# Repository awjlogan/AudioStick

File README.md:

# AudioStick

Quality audio carrier board for the Raspberry Pi Zero. A self facilitating media node.

## Description and Getting Started

This board is designed to be used with a Raspberry Pi Zero (W) to turn it into small high quality streaming audio device. It incorporates a soft power switch, which makes it easier to use in normal settings (e.g., don't need to SSH in to shutdown) and prolong the life of the SD card. The AudioStick connects directly to the standard Raspberry Pi 40pin GPIO header.

All design files and source code are under the [_Don't Be A Dick_][dbad-github] license.

### Installation on the Raspberry Pi

From a clean installation of Raspbian, log in to your Raspberry Pi and run the following 3 lines:

```shell
> sudo apt install git
> git clone https://github.com/awjlogan/audiostick.git
> cd ./audiostick
> sudo ./audiostick_setup.sh
```

The `audiostick_setup.sh` script will:
 - Install the PCM5102's configuration in the boot configuration
 - Add the `asound.conf` configuration file
 - Add the power control service
 - Shutdown the Raspberry Pi

When it is complete, you will need to remove and reconnect the power before powering on again.

### Using the AudioStick

 - When the AudioStick is off, there is no power supplied to the Raspberry Pi, so power consumption is minimised.
 - Pressing the button will power on the Raspberry Pi. The power LED will flash until the Raspberry Pi has successfully booted, at which point it will stay on.
 - To turn the AudioStick OFF, press and hold the button for at least one second. The power LED will flash until the Raspberry Pi has safely shutdown. Once the LED returns to pulsing, the Raspberry Pi is completely off and it is safe to remove the power if you wish.

### Raspberry Pi Setup

The AudioStick is intended to be used with something like MPD to allow you to connect up to any speaker (with amplifier) and get access to your local music or streaming services controlled by your phone. There are a lot of good tutorials (REVISIT add some links) available, so I won't reiterate the points here, but here are a few additional things that might be useful:

 - Change the Raspberry Pi's hostname to a meaningful name, for example `livingroompi`. This will also allow you to have multiple AudioSticks on the same network.
 - Configure your NAS (or whatever storage) to mount at boot time in `/etc/fstab`. Be aware that the system might attempt to mount the device before the network is available.
 - Disable the swap file to increase the SD card's life (`sudo apt remove dphys-swapfile`)

## Hardware

### PCB

The PCB was designed using [EAGLE][eagle-web] v9. The *.brd* and *.sch* files are provided, along with a small library of parts (*AudioStick.lbr*). A full bill of materials is provided as an *.ods* file.

### Firmware and flashing the ATtiny13A

The source for the power control microcontroller is provided, and can be compiled with the supplied Makefile. You will need to alter `Makefile` with the programmer that you are using. To compile the firmware:

`> /firmware/make`

The header **J4** on the PCB is a standard Microchip \[Atmel\] 6 pin programming header. Using your compiled firmware (or the precompiled *.hex* file), you can flash the microcontroller with e.g. an Atmel ICE. To flash the microcontroller, run:

`> /firmware/make flash`

## Change Notes

### Version 2.2

 - [x] -ELEC- Change from pogo pads to pin header for AVR ISP.

### Version 2.1

 - [x] -MECH- Mirror RasPi so connectors face Audiostick board.
 - [x] -ELEC- Move LED to PWM output pin for more interesting effects (chicken transistor in case programmer can't drive pin with LED).
 - [x] -ELEC- Remove MOSFET power switch for RasPi. Use inrush inhibitor instead.
 - [x] -ELEC- Downsize RasPi power capacitor.

### Version 2.0

Finalised release PCB, firmware, and RasPi software.

## Datasheets and useful links

- [PCM5102 DAC][pcm5102-datasheet]
- [ATtiny13A][attiny13-datasheet]

[dbad-github]: https://github.com/philsturgeon/dbad
[eagle-web]: https://www.autodesk.com/products/eagle/overview
[pcm5102-datasheet]: http://www.ti.com/product/PCM5102
[attiny13-datasheet]: https://www.microchip.com/wwwproducts/en/ATTINY13A

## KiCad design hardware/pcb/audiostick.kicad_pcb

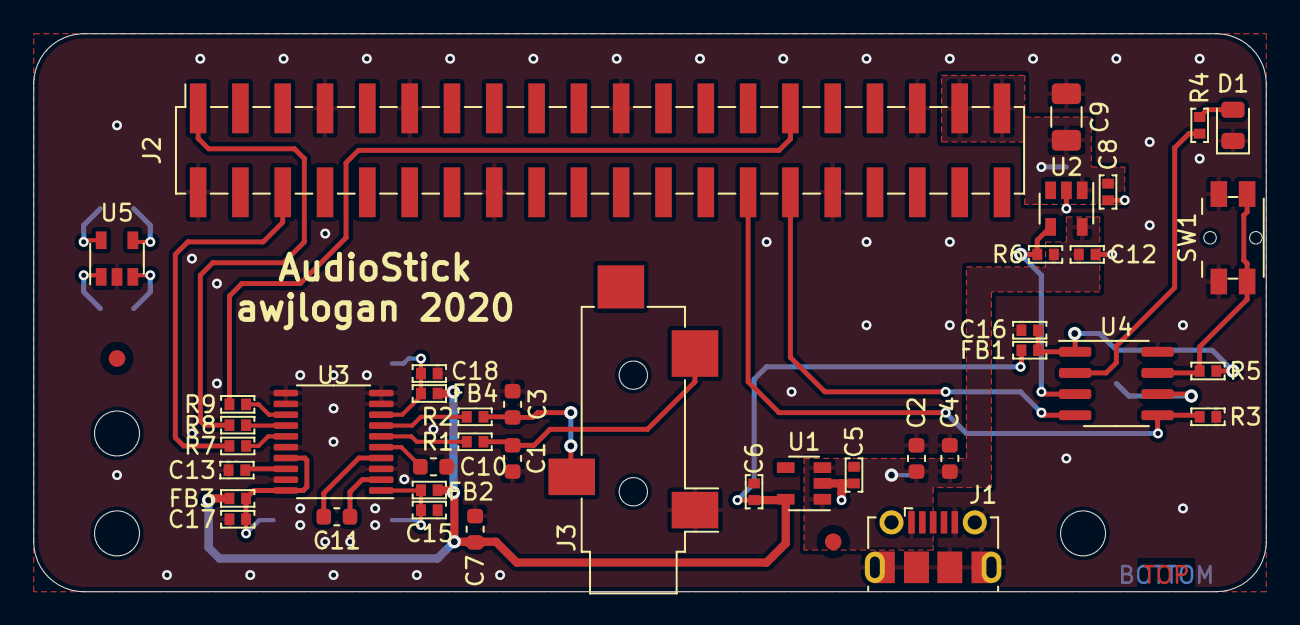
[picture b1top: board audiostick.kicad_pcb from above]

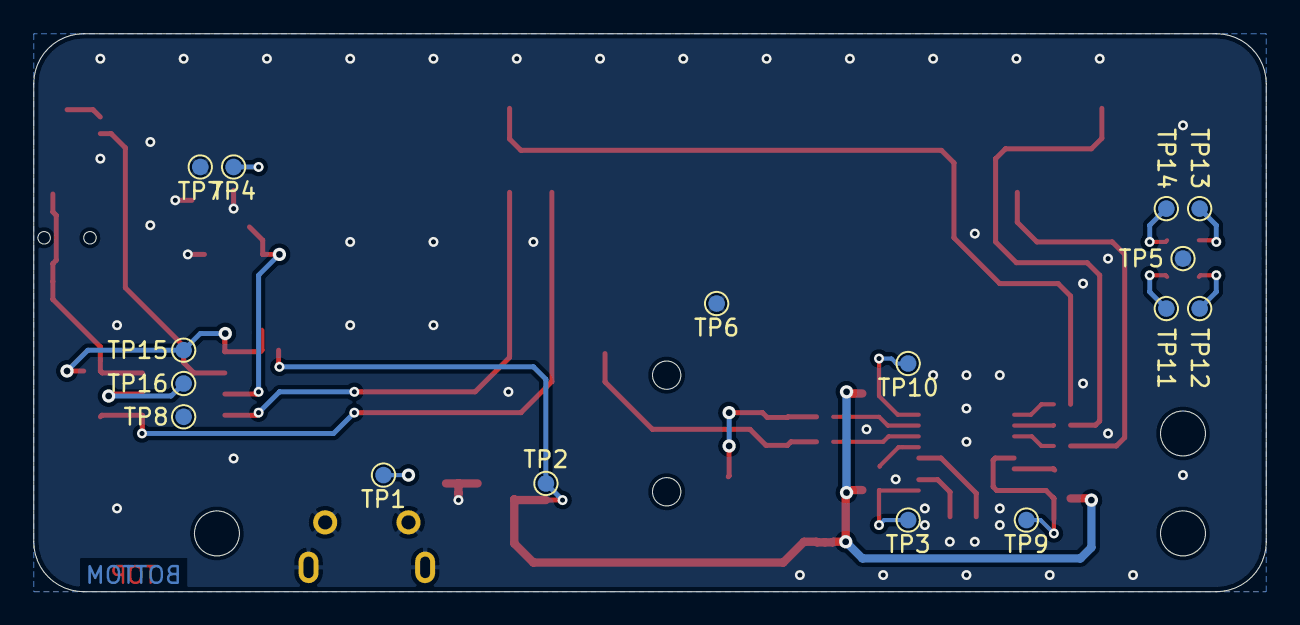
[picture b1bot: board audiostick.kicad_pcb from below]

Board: 2 copper layers, 74.0 x 33.5 mm, 61 parts (16 on the bottom side), 33 nets.

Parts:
C1, C3: 2n2; C_0603_1608Metric
C2, C4, C7, C10, C11: 2u2; C_0603_1608Metric
C5, C6, C8, C12, C13, C15, C16, C17, C18: 100n; perfect0402_C
C9: 47u; C_1206_3216Metric
D1: LED; LED_0805_2012Metric
FB1, FB2, FB3, FB4: Ferrite_Bead_Small; perfect0402_R
FID1, FID2: Fiducial; Fiducial_1mm_Mask2mm
H1, H2, H3: MountingHole; MountingHole_2.7mm_M2.5
J1: USB_B_Micro; USB_Micro-B_Molex-105017-0001
J2: Conn_02x20_Odd_Even; PinSocket_2x20_P2.54mm_Vertical_SMD
J3: AudioJack3_Switch; Jack_3.5mm_CUI_SJ-3524-SMT_Horizontal
R1, R2: 470; perfect0402_R
R3, R5, R6: 47K; perfect0402_R
R4: 330R; perfect0402_R
R7, R8, R9: 0R; perfect0402_R
SW1: SW_Push; Panasonic_EVQPUL_EVQPUC
TP1: VBUS; TestPoint_Pad_D1.0mm
TP2: 3V3A; TestPoint_Pad_D1.0mm
TP3: CPVDD; TestPoint_Pad_D1.0mm
TP4: 5V0; TestPoint_Pad_D1.0mm
TP5, TP6, TP7, TP8: GND; TestPoint_Pad_D1.0mm
TP9: DVDD; TestPoint_Pad_D1.0mm
TP10: AVDD; TestPoint_Pad_D1.0mm
TP11, TP12, TP13, TP14: WP; TestPoint_Pad_D1.0mm
TP15: 3V3; TestPoint_Pad_D1.0mm
TP16: UPDI; TestPoint_Pad_D1.0mm
U1: AP2127K-3.3; SOT-23-5
U2: AP2161W; SOT-23-5
U3: PCM5102; TSSOP-20_4.4x6.5mm_P0.65mm
U4: ATtiny202-SS; SOIC-8_3.9x4.9mm_P1.27mm
U5: AT24CS01-STUM; SOT-23-5

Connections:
+3.3VA: C6.1, C7.1, FB1.2, FB2.1, FB3.1, FB4.1, TP2.1, U1.5
+3V3: TP14.1, U5.4
+5V: C8.1, C9.1, J2.37, J2.39, TP4.1, U2.1
/3V3M: C16.1, FB1.1, R5.2, TP15.1, U4.1
/ACK: J2.28, R3.2, U4.5
/BCK: J2.29, R9.2
/DIN: J2.1, R8.2
/ID_SC: TP12.1, U5.1
/ID_SD: TP11.1, U5.3
/LED: R4.2, U4.2
/LRCK: J2.6, R7.2
/OUTL_RAW: R1.2, U3.6
/OUTR_RAW: R2.2, U3.7
/REQ: J2.30, U4.4
/SW: R5.1, SW1.2, U4.7
/~EN: R6.1, U2.4, U4.3
GND: C1.2, C2.2, C3.2, C4.2, C5.2, C6.2, C7.2, C8.2, C9.2, C10.2, C12.2, C13.2, C15.2, C16.2, C17.2, C18.2, D1.1, J1.5, J1.6, J2.2, J2.7, J2.11, J2.16, J2.21, J2.32, J2.35, J3.S, R3.1, SW1.1, TP5.1, TP6.1, TP7.1, TP8.1, U1.2, U2.2, U3.3, U3.9, U3.10, U3.11, U3.12, U3.16, U3.19, U4.8, U5.2
unnamed: C1.1, J3.T, R1.1
unnamed: C3.1, J3.R, R2.1
unnamed: C10.1, U3.5
unnamed: C11.1, U3.2
unnamed: C11.2, U3.4
unnamed: C13.1, U3.18
unnamed: C15.1, FB2.2, TP3.1, U3.1
unnamed: C17.1, FB3.2, TP9.1, U3.17, U3.20
unnamed: C18.1, FB4.2, TP10.1, U3.8
unnamed: D1.2, R4.1
unnamed: R7.1, U3.15
unnamed: R8.1, U3.14
unnamed: R9.1, U3.13
unnamed: TP13.1, U5.5
unnamed: TP16.1, U4.6
VBUS: C2.1, C4.1, C5.1, C12.1, J1.1, R6.2, TP1.1, U1.1, U1.3, U2.5

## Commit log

2019-06-14 First commit of project files
    README to be updated.
2019-08-12 Added (untested) Pi side scripts
2019-10-13 Added initial BOM, update of README, added Makefile STILL NOT TESTED!
2020-01-04 first v2 commit
2020-01-13 v2.0 changes
2020-01-13 Resolve symlink
2020-01-16 Complete revision of design - layout, connections, parts. Ready for proto run
2020-01-16 Moved text slightly
2020-01-16 Change license to DBAD
2020-01-16 Rename LICENSE to LICENSE.md
2020-01-16 Rearrange folders
2020-01-20 Final revision before manufacture
2020-01-22 Moved vias for standoffs
2020-03-16 Update BOM, start updating readme
2020-03-23 Minimum software support
2020-03-26 Some PWM effect playing
2020-04-14 Start of v3 port to KiCad
2020-04-15 Changes made
2020-04-15 Working ON/OFF mechanism
2020-04-16 Added wait states, not yet working
2020-04-17 Fix short exit from STOP_WAIT state - overflow error
2020-04-18 chmod for mds, add laser cut path
2020-04-20 Changes to setup scripts and RasPi power service
2020-04-20 Update Pi side scripts and setup
2020-04-20 Less delay needed for STOP_WAIT state
2020-04-21 Unstash changes for v3
2020-04-21 Removed old Eagle files for v3
2020-04-22 Started layout - will need to mirror RasPi connector
2020-04-23 Update of README and setup script
2020-05-03 More layout; BOM rationalisation
2020-05-04 More layout
2020-05-04 Finish preliminary layout
2020-05-04 Change EEPROM and more layout revision
2020-05-11 Start test plan and jig
2020-05-11 Removed external EEPROM, some layout changes
2020-08-11 Added rendered schematic
2020-08-31 2.0 -> 2.1 simplification, PCB rearrangement
2020-08-31 Complete rewrite start
2020-09-01 Change switch
2020-09-01 Fix airwire and clearance
2020-09-02 Refactoring of ATtiny code; update of README.md
2020-09-02 Rationalised BOM a little
2020-09-02 Update BOM
2020-09-09 Revert to EVQ switch
2020-09-09 Change switch in BOM
2020-09-14 sync to remote
2020-11-23 Update board, BOM, and firmware
2020-12-29 Fixed RasPi setup script and README
2021-01-15 Remove unused STOP_WAIT state
2021-02-15 Real HW in hand
2021-02-15 Changed pogo points for proper header, silly idea!
2021-02-16 Confirm LED pulse working
2021-02-28 Finish schematic/layout changes
2021-02-28 Adding LED pulse effect
2021-02-28 Update README and Eagle lib
2021-05-20 * Add case STLs
2021-11-02 Disable default sound driver
2022-10-01 - install git as first step
2022-10-01 Remove redundant setup information
